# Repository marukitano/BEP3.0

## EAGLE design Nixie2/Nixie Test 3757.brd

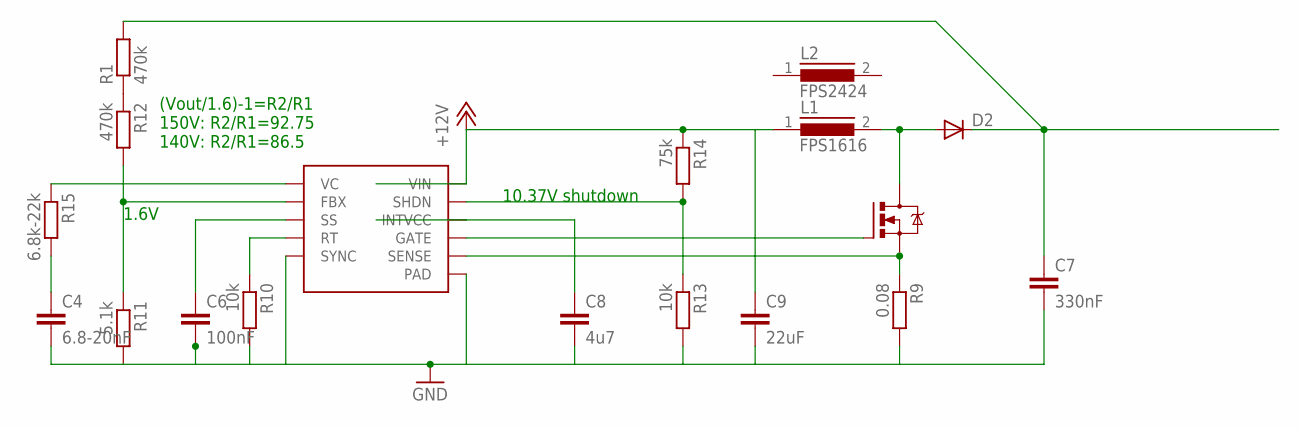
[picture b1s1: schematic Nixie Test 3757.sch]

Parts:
C4: 6.8-20nF; C0805K
C6: 100nF; C0805K
C7: 330nF; C1812
C8: 4u7; C1206K
C9: 22uF; C1210K
D2: DIODE-DO219AB; DO219AB
L1: FPS1616; 1616FPS_22UH
L2: FPS2424; 242408FPS_22UH
Q1: N-MOSFET-TO252-DPAK; TO252
R1, R12: 470k; R0805
R9: 0.08; R0805
R10, R13: 10k; R0805
R11: 5.1k; R0805
R14: 75k; R0805
R15: 6.8k-22k; R0805
U2: LT3757MSOP-10; MSOP-10

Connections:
+12V: C9.1, L1.1, R14.1, U2.10 (VIN)
GND: C4.2, C6.2, C7.2, C8.2, C9.2, R9.2, R10.2, R11.2, R13.2, U2.5 (SYNC), U2.PAD
unnamed: R1.1, R12.1
unnamed: Q1.1 (G), U2.7 (GATE)
unnamed: R11.1, R12.2, U2.2 (FBX)
unnamed: D2.A, L1.2, Q1.3 (D)
unnamed: C7.1, D2.C, R1.2
unnamed: C6.1, U2.3 (SS)
unnamed: R10.1, U2.4 (RT)
unnamed: Q1.2 (S), R9.1, U2.6 (SENSE)
unnamed: R13.1, R14.2, U2.9 (SHDN)
unnamed: C4.1, R15.2
unnamed: R15.1, U2.1 (VC)
unnamed: C8.1, U2.8 (INTVCC)

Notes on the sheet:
10.37V shutdown
1.6V
(Vout/1.6)-1=R2/R1 150V: R2/R1=92.75 140V: R2/R1=86.5

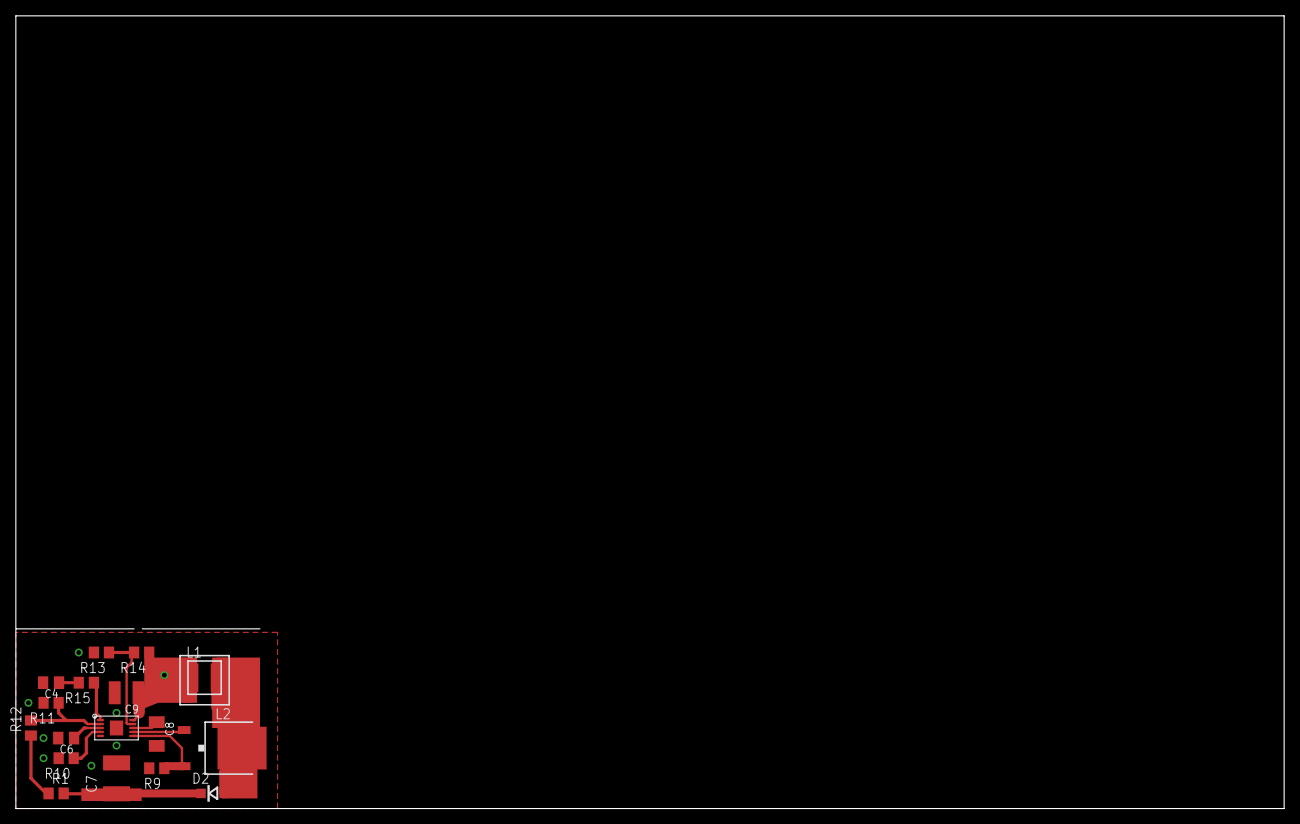
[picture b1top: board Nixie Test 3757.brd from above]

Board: 2 copper layers, 160.0 x 100.0 mm, 18 parts (0 on the bottom side), 14 nets.

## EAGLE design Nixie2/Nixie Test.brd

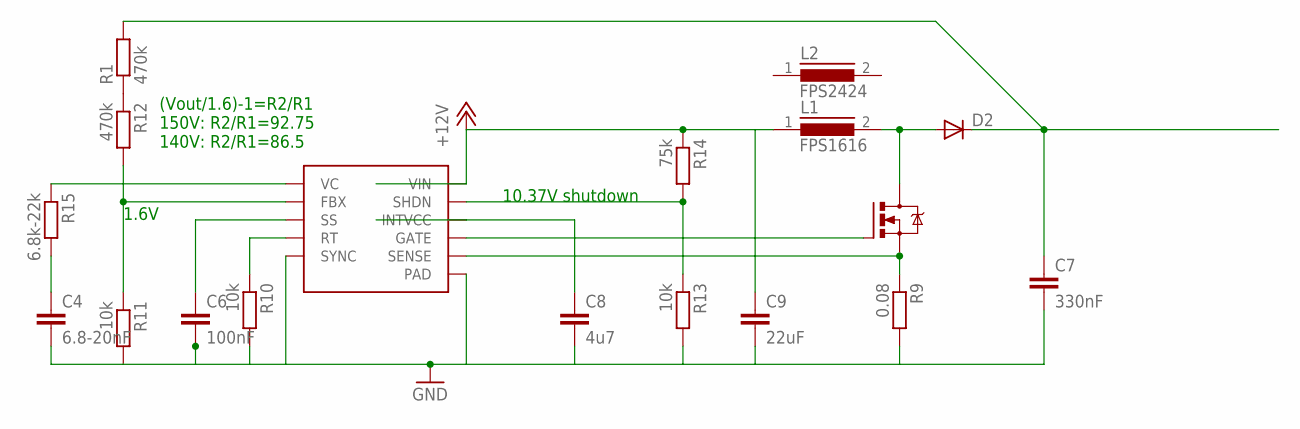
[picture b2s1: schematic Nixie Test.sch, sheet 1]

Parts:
C4: 6.8-20nF; C0805K
C6: 100nF; C0805K
C7: 330nF; C1812
C8: 4u7; C1206K
C9: 22uF; C1210K
D2: DIODE-DO219AB; DO219AB
L1: FPS1616; 1616FPS_22UH
L2: FPS2424; 242408FPS_22UH
Q1: N-MOSFET-TO252-DPAK; TO252
R1, R12: 470k; R0805
R9: 0.08; R0805
R10, R11, R13: 10k; R0805
R14: 75k; R0805
R15: 6.8k-22k; R0805
U2: LT3757MSOP-10; MSOP-10

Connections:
+12V: C9.1, L1.1, R14.1, U2.10 (VIN); also elsewhere on the board
GND: C4.2, C6.2, C7.2, C8.2, C9.2, R9.2, R10.2, R11.2, R13.2, U2.5 (SYNC), U2.PAD; also elsewhere on the board
unnamed: R1.1, R12.1
unnamed: Q1.1 (G), U2.7 (GATE)
unnamed: R11.1, R12.2, U2.2 (FBX)
unnamed: D2.A, L1.2, Q1.3 (D)
unnamed: C7.1, D2.C, R1.2
unnamed: C6.1, U2.3 (SS)
unnamed: R10.1, U2.4 (RT)
unnamed: Q1.2 (S), R9.1, U2.6 (SENSE)
unnamed: R13.1, R14.2, U2.9 (SHDN)
unnamed: C4.1, R15.2
unnamed: R15.1, U2.1 (VC)
unnamed: C8.1, U2.8 (INTVCC)

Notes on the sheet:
10.37V shutdown
1.6V
(Vout/1.6)-1=R2/R1 150V: R2/R1=92.75 140V: R2/R1=86.5

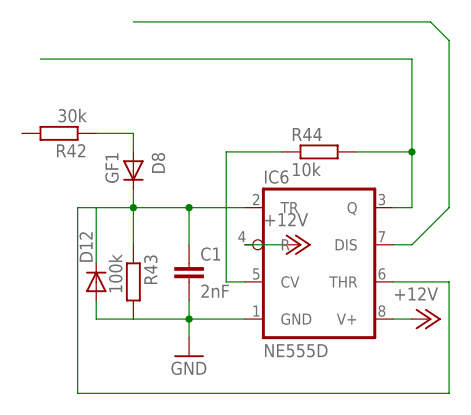
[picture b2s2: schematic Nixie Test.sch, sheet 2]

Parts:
C1: 2nF; C1206K
D8: GF1; SMA-DO214AC
D12: DIODE-DO214AA; DO214AA
IC6: NE555D; SO08
R42: 30k; R0805
R43: 100k; R0805
R44: 10k; R0805

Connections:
+12V: IC6.4 (R), IC6.8 (V+); also elsewhere on the board
GND: C1.2, D12.A, IC6.1 (GND), R43.2; also elsewhere on the board
unnamed: D8.A, R42.1
unnamed: IC6.3 (Q), R44.2
unnamed: IC6.5 (CV), R44.1
unnamed: C1.1, D8.K (C), D12.C, IC6.2 (TR), IC6.6 (THR), R43.1

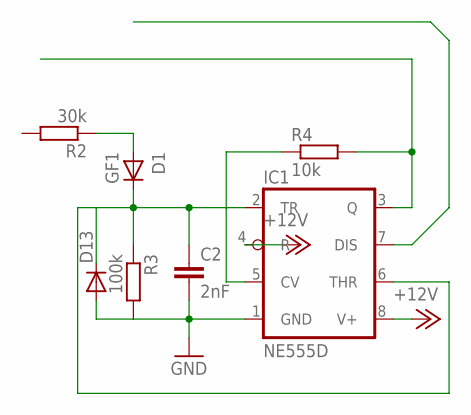
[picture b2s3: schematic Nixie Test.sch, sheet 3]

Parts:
C2: 2nF; C1206K
D1: GF1; SMA-DO214AC
D13: DIODE-DO214AA; DO214AA
IC1: NE555D; SO08
R2: 30k; R0805
R3: 100k; R0805
R4: 10k; R0805

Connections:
+12V: IC1.4 (R), IC1.8 (V+); also elsewhere on the board
GND: C2.2, D13.A, IC1.1 (GND), R3.2; also elsewhere on the board
unnamed: D1.A, R2.1
unnamed: IC1.5 (CV), R4.1
unnamed: C2.1, D1.K (C), D13.C, IC1.2 (TR), IC1.6 (THR), R3.1
unnamed: IC1.3 (Q), R4.2

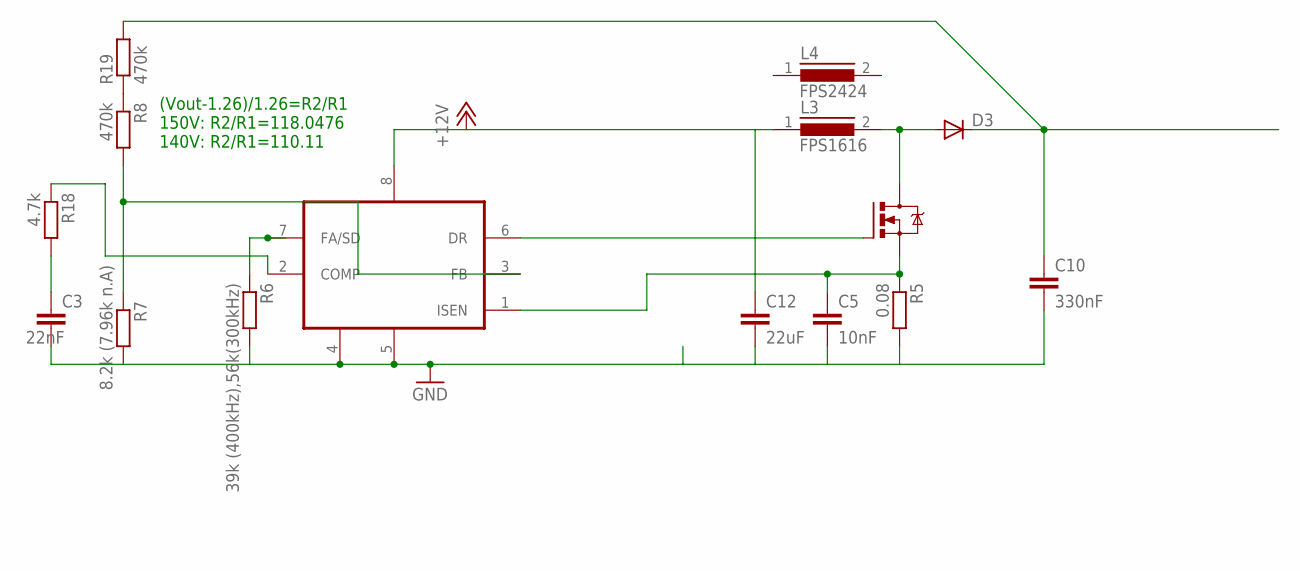
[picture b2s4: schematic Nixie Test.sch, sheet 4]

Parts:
C3: 22nF; C0805K
C5: 10nF; C0805K
C10: 330nF; C1812
C12: 22uF; C1210K
D3: DIODE-DO219AB; DO219AB
L3: FPS1616; 1616FPS_22UH
L4: FPS2424; 242408FPS_22UH
Q2: N-MOSFET-TO252-DPAK; TO252
R5: 0.08; R0805
R6: 39k (400kHz),56k(300kHz); R0805
R7: 8.2k (7.96k n.A); R0805
R8, R19: 470k; R0805
R18: 4.7k; R0805
U3: LM3478; MSOP08

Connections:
+12V: C12.1, L3.1, U3.8 (VIN); also elsewhere on the board
GND: C3.2, C5.2, C10.2, C12.2, R5.2, R6.2, R7.2, U3.4 (AGND), U3.5 (PGND); also elsewhere on the board
unnamed: Q2.1 (G), U3.6 (DR)
unnamed: R7.1, R8.2, U3.3 (FB)
unnamed: D3.A, L3.2, Q2.3 (D)
unnamed: C10.1, D3.C, R19.2
unnamed: R18.1, U3.2 (COMP)
unnamed: R6.1, U3.7 (FA/SD)
unnamed: C5.1, Q2.2 (S), R5.1, U3.1 (ISEN)
unnamed: C3.1, R18.2
unnamed: R8.1, R19.1

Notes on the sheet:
(Vout-1.26)/1.26=R2/R1 150V: R2/R1=118.0476 140V: R2/R1=110.11

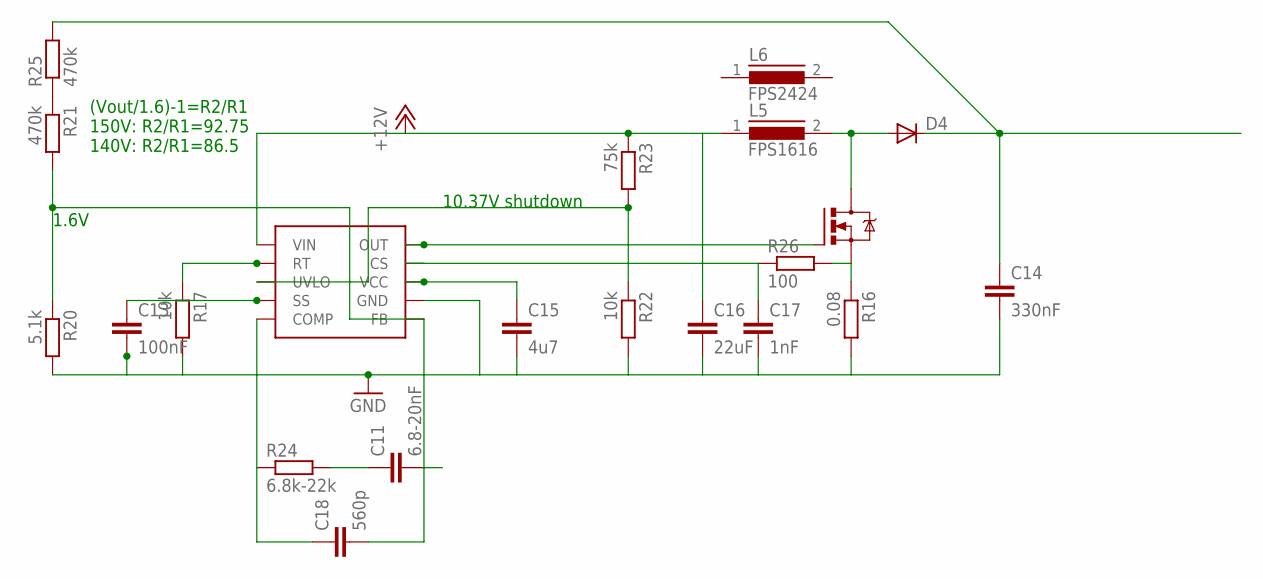
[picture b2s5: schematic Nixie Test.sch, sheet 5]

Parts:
C11: 6.8-20nF; C0805K
C13: 100nF; C0805K
C14: 330nF; C1812
C15: 4u7; C1206K
C16: 22uF; C1210K
C17: 1nF; C0805K
C18: 560p; C0805K
D4: DIODE-DO219AB; DO219AB
L5: FPS1616; 1616FPS_22UH
L6: FPS2424; 242408FPS_22UH
Q3: N-MOSFET-TO252-DPAK; TO252
R16: 0.08; R0805
R17, R22: 10k; R0805
R20: 5.1k; R0805
R21, R25: 470k; R0805
R23: 75k; R0805
R24: 6.8k-22k; R0805
R26: 100; R0805
U4: LM5022MSOP-10; MSOP-10-NOPAD

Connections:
+12V: C16.1, L5.1, R23.1, U4.1 (VIN); also elsewhere on the board
GND: C13.2, C14.2, C15.2, C16.2, C17.2, R16.2, R17.2, R20.2, R22.2, U4.6 (GND); also elsewhere on the board
unnamed: Q3.1 (G), U4.5 (OUT)
unnamed: C11.2, C18.2, R20.1, R21.2, U4.2 (FB)
unnamed: D4.A, L5.2, Q3.3 (D)
unnamed: C14.1, D4.C, R25.2
unnamed: C13.1, U4.10 (SS)
unnamed: R17.1, U4.9 (RT)
unnamed: Q3.2 (S), R16.1, R26.2
unnamed: R22.1, R23.2, U4.7 (UVLO)
unnamed: C11.1, R24.2
unnamed: C18.1, R24.1, U4.3 (COMP)
unnamed: C15.1, U4.4 (VCC)
unnamed: R21.1, R25.1
unnamed: C17.1, R26.1, U4.8 (CS)

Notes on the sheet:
10.37V shutdown
1.6V
(Vout/1.6)-1=R2/R1 150V: R2/R1=92.75 140V: R2/R1=86.5

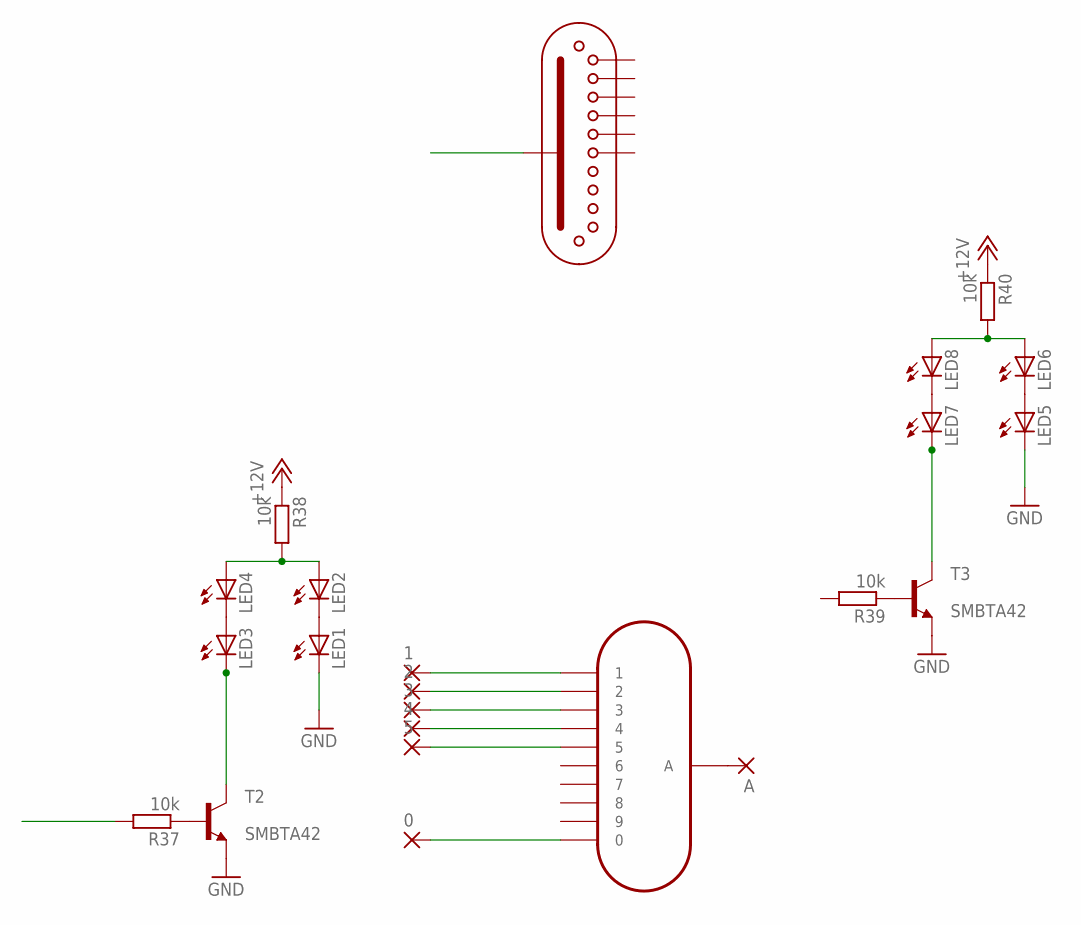
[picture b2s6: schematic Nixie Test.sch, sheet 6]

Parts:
0, 1, 2, 3, 4, 5: SMD2; SMD1,27-2,54
A: SMD2; SMD1,27-2,54
LED1, LED2, LED3, LED4, LED5, LED6, LED7, LED8: LED3MM
N1: IN-12A-IN-12; IN-12
R37, R38, R39, R40: 10k; R0805
T2, T3: MMBTA42LT1-NPN-SOT23-BEC; SOT23-BEC
U$3: ZM1020

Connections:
+12V: R38.1, R40.1; also elsewhere on the board
GND: LED1.K (C), LED5.K (C), T2.E, T3.E; also elsewhere on the board
unnamed: LED1.A, LED2.K (C)
unnamed: LED3.A, LED4.K (C)
unnamed: R37.1, T2.B
unnamed: LED3.K (C), T2.C
unnamed: LED2.A, LED4.A, R38.2
unnamed: 0.1, N1.0
unnamed: 1.1, N1.1
unnamed: 2.1, N1.2
unnamed: 3.1, N1.3
unnamed: 4.1, N1.4
unnamed: 5.1, N1.5
unnamed: A.1, N1.A
unnamed: LED5.A, LED6.K (C)
unnamed: LED7.A, LED8.K (C)
unnamed: R39.1, T3.B
unnamed: LED7.K (C), T3.C
unnamed: LED6.A, LED8.A, R40.2

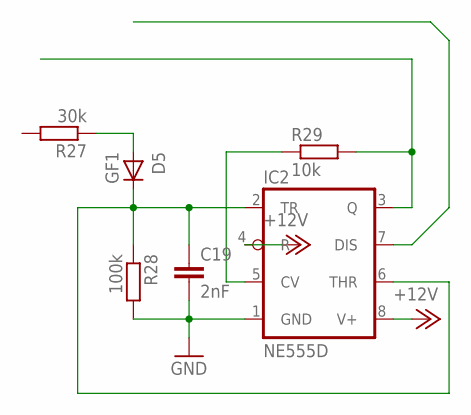
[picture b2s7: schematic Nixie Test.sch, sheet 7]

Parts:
C19: 2nF; C1206K
D5: GF1; SMA-DO214AC
IC2: NE555D; SO08
R27: 30k; R0805
R28: 100k; R0805
R29: 10k; R0805

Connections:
+12V: IC2.4 (R), IC2.8 (V+); also elsewhere on the board
GND: C19.2, IC2.1 (GND), R28.2; also elsewhere on the board
unnamed: D5.A, R27.1
unnamed: IC2.5 (CV), R29.1
unnamed: C19.1, D5.K (C), IC2.2 (TR), IC2.6 (THR), R28.1
unnamed: IC2.3 (Q), R29.2

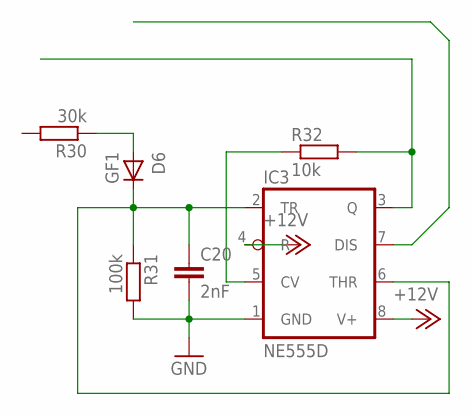
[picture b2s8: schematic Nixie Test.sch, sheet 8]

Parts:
C20: 2nF; C1206K
D6: GF1; SMA-DO214AC
IC3: NE555D; SO08
R30: 30k; R0805
R31: 100k; R0805
R32: 10k; R0805

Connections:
+12V: IC3.4 (R), IC3.8 (V+); also elsewhere on the board
GND: C20.2, IC3.1 (GND), R31.2; also elsewhere on the board
unnamed: D6.A, R30.1
unnamed: IC3.5 (CV), R32.1
unnamed: C20.1, D6.K (C), IC3.2 (TR), IC3.6 (THR), R31.1
unnamed: IC3.3 (Q), R32.2

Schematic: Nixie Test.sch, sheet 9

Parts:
C21: 2nF; C1206K
D7: GF1; SMA-DO214AC
IC4: NE555D; SO08
R33: 30k; R0805
R34: 100k; R0805
R35: 10k; R0805

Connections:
+12V: IC4.4 (R), IC4.8 (V+); also elsewhere on the board
GND: C21.2, IC4.1 (GND), R34.2; also elsewhere on the board
unnamed: D7.A, R33.1
unnamed: IC4.5 (CV), R35.1
unnamed: C21.1, D7.K (C), IC4.2 (TR), IC4.6 (THR), R34.1
unnamed: IC4.3 (Q), R35.2

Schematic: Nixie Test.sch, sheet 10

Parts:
C22: 2nF; C1206K
D9: GF1; SMA-DO214AC
IC5: NE555D; SO08
R36: 30k; R0805
R41: 100k; R0805
R45: 10k; R0805

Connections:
+12V: IC5.4 (R), IC5.8 (V+); also elsewhere on the board
GND: C22.2, IC5.1 (GND), R41.2; also elsewhere on the board
unnamed: D9.A, R36.1
unnamed: IC5.5 (CV), R45.1
unnamed: C22.1, D9.K (C), IC5.2 (TR), IC5.6 (THR), R41.1
unnamed: IC5.3 (Q), R45.2

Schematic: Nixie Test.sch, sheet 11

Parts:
C23: 6.8-20nF; C0805K
C24: 100nF; C0805K
C25: 330nF; C1812
C26: 4u7; C1206K
C27: 22uF; C1210K
D10: DIODE-DO219AB; DO219AB
L7: FPS1616; 1616FPS_22UH
L8: FPS2424; 242408FPS_22UH
Q4: N-MOSFET-TO252-DPAK; TO252
R46: 0.08; R0805
R47, R50: 10k; R0805
R48: 5.1k; R0805
R49, R53: 470k; R0805
R51: 75k; R0805
R52: 6.8k-22k; R0805
U1: LT3757MSOP-10; MSOP-10

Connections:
+12V: C27.1, L7.1, R51.1, U1.10 (VIN); also elsewhere on the board
GND: C23.2, C24.2, C25.2, C26.2, C27.2, R46.2, R47.2, R48.2, R50.2, U1.5 (SYNC), U1.PAD; also elsewhere on the board
unnamed: Q4.1 (G), U1.7 (GATE)
unnamed: R48.1, R49.2, U1.2 (FBX)
unnamed: D10.A, L7.2, Q4.3 (D)
unnamed: C25.1, D10.C, R53.2
unnamed: C24.1, U1.3 (SS)
unnamed: R47.1, U1.4 (RT)
unnamed: Q4.2 (S), R46.1, U1.6 (SENSE)
unnamed: R50.1, R51.2, U1.9 (SHDN)
unnamed: C23.1, R52.2
unnamed: R52.1, U1.1 (VC)
unnamed: C26.1, U1.8 (INTVCC)
unnamed: R49.1, R53.1

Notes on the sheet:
10.37V shutdown
1.6V
(Vout/1.6)-1=R2/R1 150V: R2/R1=92.75 140V: R2/R1=86.5

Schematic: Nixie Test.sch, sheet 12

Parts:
C28: 2nF; C1206K
D11: GF1; SMA-DO214AC
IC7: NE555D; SO08
R54: 30k; R0805
R55: 100k; R0805
R56: 10k; R0805

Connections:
+12V: IC7.4 (R), IC7.8 (V+); also elsewhere on the board
GND: C28.2, IC7.1 (GND), R55.2; also elsewhere on the board
unnamed: D11.A, R54.1
unnamed: IC7.5 (CV), R56.1
unnamed: C28.1, D11.K (C), IC7.2 (TR), IC7.6 (THR), R55.1
unnamed: IC7.3 (Q), R56.2

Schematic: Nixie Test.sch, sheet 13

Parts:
12, 13, 14, 15, 16, 17, 18, 19, 20, 21: SMD2; SMD1,27-2,54
A2: SMD2; SMD1,27-2,54
LED17, LED18, LED19, LED20: LED_PLCC6; PLCC6
LED21, LED22: LED_LRTB_G6TG; PLCC6
N3: IN-12A-IN-12; IN-12
R71, R72, R73, R74, R75, R76, R77, R78: 10k; R0805
U$5, U$6, U$8, U$9, U$12, U$13: PLCC2
U$7, U$10, U$11: ZM1020

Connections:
GND: LED18.C3 (C), LED20.C3 (C), LED22.C2 (C), LED22.C3 (C), U$8.C, U$9.C, U$12.C, U$13.C; also elsewhere on the board
unnamed: U$5.C, U$8.A
unnamed: U$6.C, U$9.A
unnamed: R72.2, U$6.A
unnamed: R71.2, U$5.A
unnamed: 12.1, R71.1, R72.1
unnamed: LED17.C3 (C), LED18.A3 (A)
unnamed: LED19.C3 (C), LED20.A3 (A)
unnamed: LED19.A3 (A), R74.2
unnamed: LED17.A3 (A), R73.2
unnamed: 13.1, R73.1, R74.1
unnamed: LED21.C2 (C), LED22.A2 (A)
unnamed: LED21.C3 (C), LED22.A3 (A)
unnamed: LED21.A3 (A), R76.2
unnamed: LED21.A2 (A), R75.2
unnamed: 14.1, R75.1, R76.1
unnamed: 15.1, N3.0
unnamed: 16.1, N3.1
unnamed: 17.1, N3.2
unnamed: 18.1, N3.3
unnamed: 19.1, N3.4
unnamed: 20.1, N3.5
unnamed: A2.1, N3.A
unnamed: R78.2, U$13.A
unnamed: R77.2, U$12.A
unnamed: 21.1, R77.1, R78.1

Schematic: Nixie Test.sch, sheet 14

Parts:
D14, D15, D16: 1N4148; SOD323-W
PAD1, PAD2, PAD3, PAD4: WIREPAD1,6/0,8; 1,6/0,8
R57, R58, R59: R-EU_R0805; R0805
T1, T4, T5: BSP78; SOT223
X3: F09D

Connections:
CTS: R57.1, X3.8; also elsewhere on the board
DCD: R59.1, X3.1; also elsewhere on the board
DSR: R58.1, X3.6; also elsewhere on the board
DTR: D16.A, X3.4; also elsewhere on the board
GND: PAD4.1, T1.3 (S), T4.3 (S), T5.3 (S), X3.5; also elsewhere on the board
unnamed: D16.C, T5.1 (G)
unnamed: D15.C, T4.1 (G)
unnamed: D14.C, T1.1 (G)
unnamed: PAD1.1, R57.2, T1.2 (D)
unnamed: PAD2.1, R58.2, T4.2 (D)
unnamed: PAD3.1, R59.2, T5.2 (D)
unnamed: D14.A, X3.7
RTS: D15.A, X3.3; also elsewhere on the board

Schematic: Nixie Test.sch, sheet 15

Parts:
D17, D18, D19: 1N4148; SOD323-W
PAD5, PAD6, PAD7, PAD8: WIREPAD1,6/0,8; 1,6/0,8
R60, R61, R62: R-EU_R0805; R0805
T6, T7, T8: BSP78; SOT223
X1: F09D

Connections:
CTS: R60.1, X1.8; also elsewhere on the board
DCD: R62.1, X1.1; also elsewhere on the board
DSR: R61.1, X1.6; also elsewhere on the board
DTR: D19.A, X1.4; also elsewhere on the board
GND: PAD8.1, T6.3 (S), T7.3 (S), T8.3 (S), X1.5; also elsewhere on the board
unnamed: D19.C, T8.1 (G)
unnamed: D18.C, T7.1 (G)
unnamed: D17.C, T6.1 (G)
unnamed: PAD5.1, R60.2, T6.2 (D)
unnamed: PAD6.1, R61.2, T7.2 (D)
unnamed: PAD7.1, R62.2, T8.2 (D)
unnamed: D17.A, X1.7
RTS: D18.A, X1.3; also elsewhere on the board

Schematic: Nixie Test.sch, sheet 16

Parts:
D20, D21, D22: 1N4148; SOD323-W
PAD9, PAD10, PAD11, PAD12: WIREPAD1,6/0,8; 1,6/0,8
R63, R64, R65: R-EU_R0805; R0805
T9, T10, T11: BSP78; SOT223
X2: F09D

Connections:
CTS: R63.1, X2.8; also elsewhere on the board
DCD: R65.1, X2.1; also elsewhere on the board
DSR: R64.1, X2.6; also elsewhere on the board
DTR: D22.A, X2.4; also elsewhere on the board
GND: PAD12.1, T9.3 (S), T10.3 (S), T11.3 (S), X2.5; also elsewhere on the board
unnamed: D22.C, T11.1 (G)
unnamed: D21.C, T10.1 (G)
unnamed: D20.C, T9.1 (G)
unnamed: PAD9.1, R63.2, T9.2 (D)
unnamed: PAD10.1, R64.2, T10.2 (D)
unnamed: PAD11.1, R65.2, T11.2 (D)
unnamed: D20.A, X2.7
RTS: D21.A, X2.3; also elsewhere on the board

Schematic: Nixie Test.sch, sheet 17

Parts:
D24, D25, D26: 1N4148; SOD323-W
PAD13, PAD14, PAD15, PAD16: WIREPAD1,6/0,8; 1,6/0,8
R66, R67, R68: R-EU_R0805; R0805
T12, T13, T14: BSP78; SOT223
X4: F09D

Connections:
CTS: R66.1, X4.8; also elsewhere on the board
DCD: R68.1, X4.1; also elsewhere on the board
DSR: R67.1, X4.6; also elsewhere on the board
DTR: D26.A, X4.4; also elsewhere on the board
GND: PAD16.1, T12.3 (S), T13.3 (S), T14.3 (S), X4.5; also elsewhere on the board
unnamed: D26.C, T14.1 (G)
unnamed: D25.C, T13.1 (G)
unnamed: D24.C, T12.1 (G)
unnamed: PAD13.1, R66.2, T12.2 (D)
unnamed: PAD14.1, R67.2, T13.2 (D)
unnamed: PAD15.1, R68.2, T14.2 (D)
unnamed: D24.A, X4.7
RTS: D25.A, X4.3; also elsewhere on the board

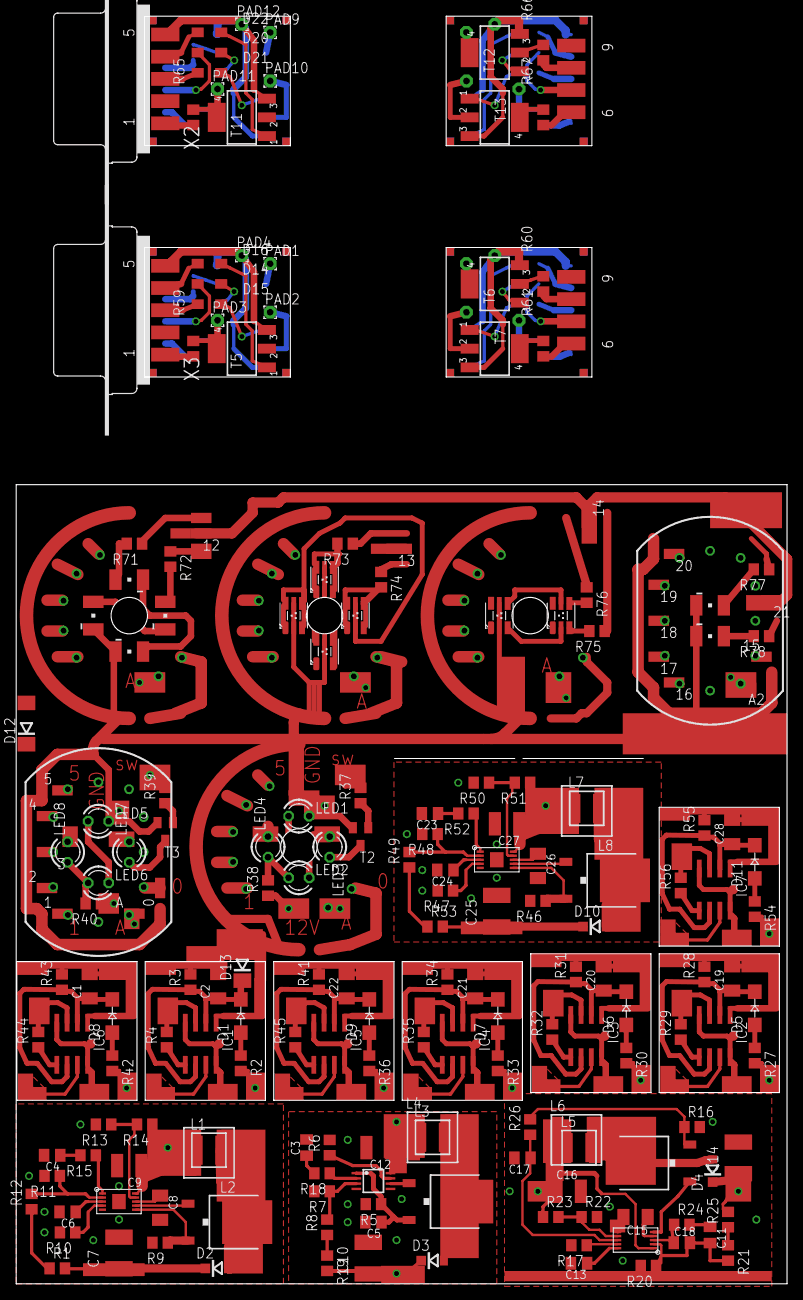
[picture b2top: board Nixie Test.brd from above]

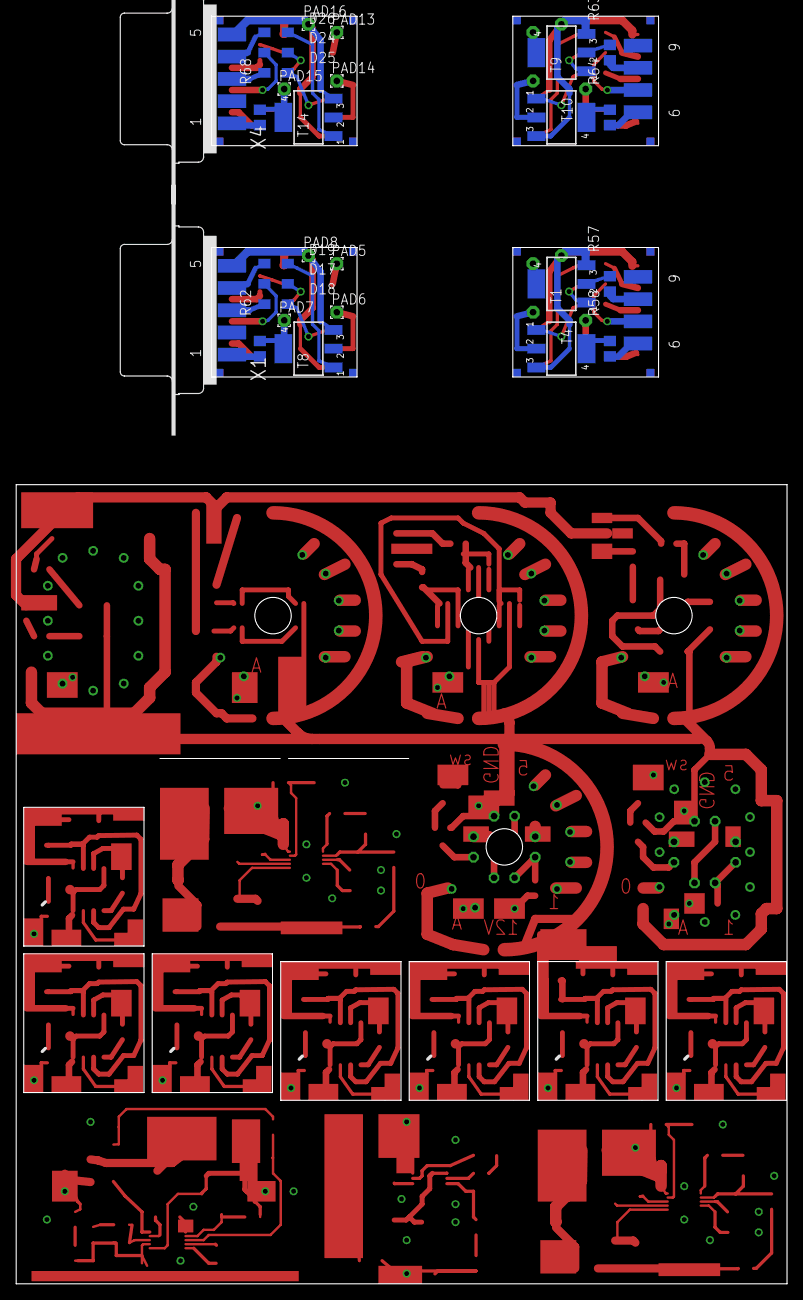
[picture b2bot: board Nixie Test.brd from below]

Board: 2 copper layers, 95.2 x 156.6 mm, 230 parts (28 on the bottom side), 151 nets.

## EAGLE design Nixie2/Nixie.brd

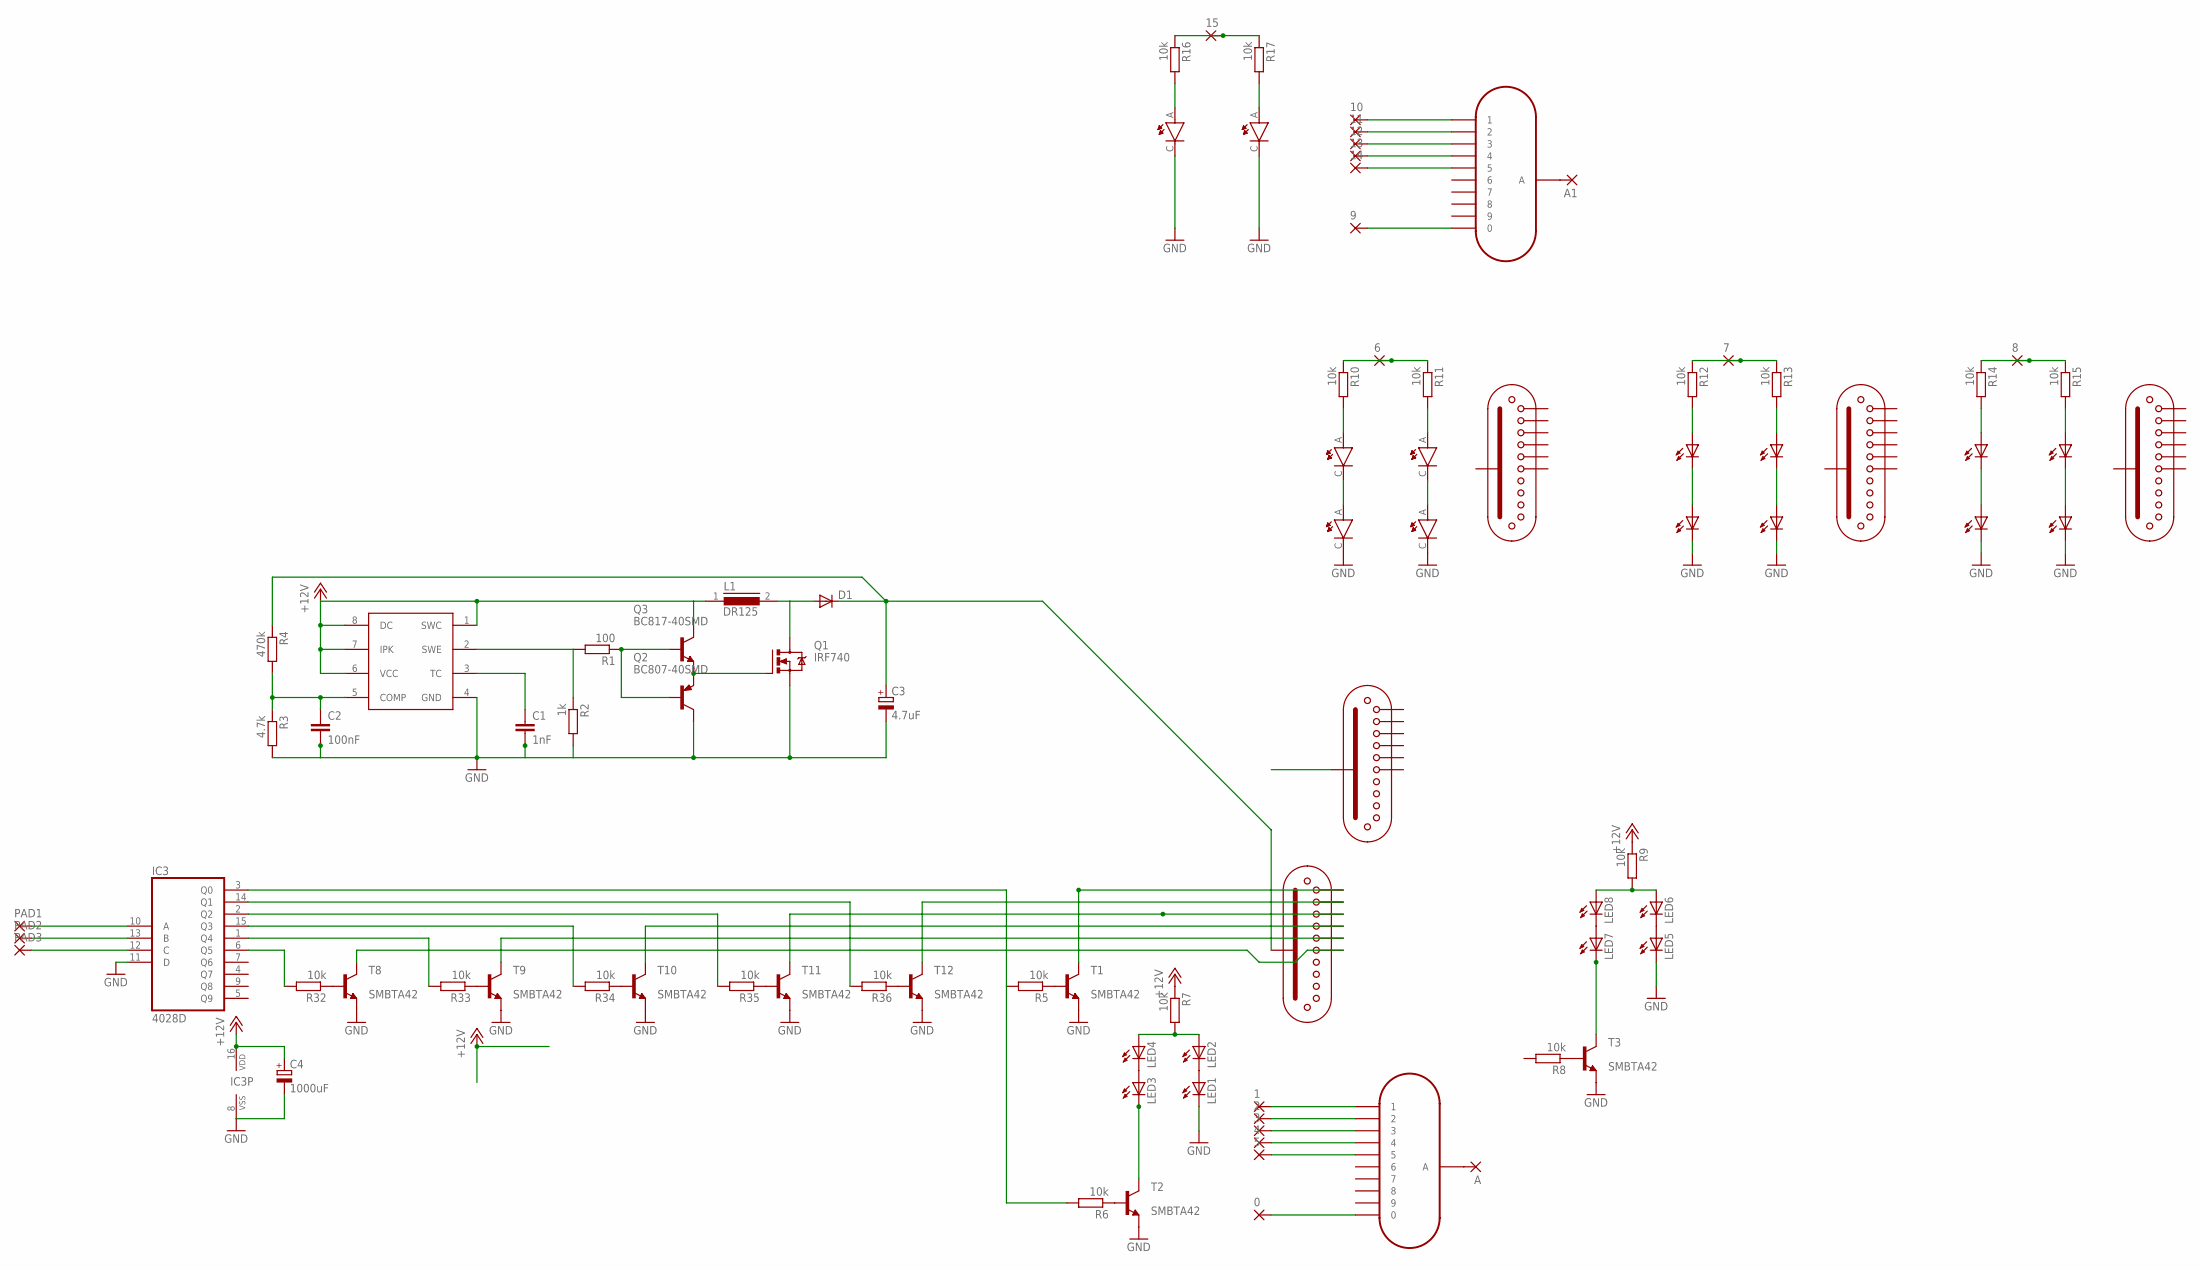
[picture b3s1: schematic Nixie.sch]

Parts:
0, 1, 2, 3, 4, 5, 6, 7, 8, 9, 10, 11, 12, 13, 14, 15: SMD2; SMD1,27-2,54
A, A1: SMD2; SMD1,27-2,54
C1: 1nF; C0805K
C2: 100nF; C0805K
C3: 4.7uF; E5-10,5
C4: 1000uF; E5-10,5
D1: DIODE-DO214AC; DO214AC
IC3: 4028D; SO16
L1: DR125
LED1, LED2, LED3, LED4, LED5, LED6, LED7, LED8: LED3MM
LED9, LED10, LED11, LED12: LED_PLCC6; PLCC6
LED13, LED14: LED_LRTB_G6TG; PLCC6
N1, N2: IN-12A-IN-12; IN-12
PAD1, PAD2, PAD3: 1,6/0,8
Q1: IRF740; TO220BV
Q2: BC807-40SMD; SOT23-BEC
Q3: BC817-40SMD; SOT23-BEC
R1: 100; R0805
R2: 1k; R0805
R3: 4.7k; R0805
R4: 470k; R0805
R5, R6, R7, R8, R9, R10, R11, R12, R13, R14, R15, R16, R17, R32, R33, R34, R35, R36: 10k; R0805
T1, T2, T3, T8, T9, T10, T11, T12: MMBTA42LT1-NPN-SOT23-BEC; SOT23-BEC
U$1, U$3, U$6, U$9, U$11: ZM1020
U$2: MC33063/MC34063D; SO08
U$4, U$5, U$7, U$8, U$10, U$12: PLCC2

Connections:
+12V: C4.+, IC3.16 (VDD), L1.1, Q3.C, R7.1, R9.1, U$2.1 (SWC), U$2.6 (VCC), U$2.7 (IPK), U$2.8 (DC)
GND: C1.2, C2.2, C3.-, C4.-, IC3.8 (VSS), IC3.11 (D), LED1.K (C), LED5.K (C), LED10.C3 (C), LED12.C3 (C), LED14.C2 (C), LED14.C3 (C), Q1.S, Q2.C, R2.2, R3.2, T1.E, T2.E, T3.E, T8.E, T9.E, T10.E, T11.E, T12.E, U$2.4 (GND), U$7.C, U$8.C, U$10.C, U$12.C
unnamed: C1.1, U$2.3 (TC)
unnamed: IC3.10 (A), PAD1.1
unnamed: IC3.13 (B), PAD2.1
unnamed: D1.A, L1.2, Q1.D
unnamed: C2.1, R3.1, R4.2, U$2.5 (COMP)
unnamed: IC3.3 (Q0), R5.2, R6.2
unnamed: R1.2, R2.1, U$2.2 (SWE)
unnamed: C3.+, D1.C, R4.1, U$1.12 (A)
unnamed: Q1.G, Q2.E, Q3.E
unnamed: Q2.B, Q3.B, R1.1
unnamed: IC3.12 (C), PAD3.1
unnamed: R5.1, T1.B
unnamed: T1.C, U$1.11 (0)
unnamed: LED1.A, LED2.K (C)
unnamed: LED3.A, LED4.K (C)
unnamed: R6.1, T2.B
unnamed: R32.1, T8.B
unnamed: LED3.K (C), T2.C
unnamed: LED2.A, LED4.A, R7.2
unnamed: 0.1, N1.0
unnamed: 1.1, N1.1
unnamed: 2.1, N1.2
unnamed: 3.1, N1.3
unnamed: 4.1, N1.4
unnamed: 5.1, N1.5
unnamed: IC3.14 (Q1), R36.2
unnamed: IC3.2 (Q2), R35.2
unnamed: T10.C, U$1.3
unnamed: A.1, N1.A
unnamed: LED5.A, LED6.K (C)
unnamed: LED7.A, LED8.K (C)
unnamed: R8.1, T3.B
unnamed: LED7.K (C), T3.C
unnamed: LED6.A, LED8.A, R9.2
unnamed: T9.C, U$1.4
unnamed: R34.1, T10.B
unnamed: U$4.C, U$7.A
unnamed: U$5.C, U$8.A
unnamed: R11.2, U$5.A
unnamed: R10.2, U$4.A
unnamed: R33.1, T9.B
unnamed: R35.1, T11.B
unnamed: 6.1, R10.1, R11.1
unnamed: LED11.C3 (C), LED12.A3 (A)
unnamed: IC3.6 (Q5), R32.2
unnamed: R36.1, T12.B
unnamed: T8.C, U$1.5
unnamed: IC3.1 (Q4), R33.2
unnamed: IC3.15 (Q3), R34.2
unnamed: T11.C, U$1.2
unnamed: T12.C, U$1.1
unnamed: LED11.A3 (A), R13.2
unnamed: LED9.A3 (A), R12.2
unnamed: 7.1, R12.1, R13.1
unnamed: LED9.C3 (C), LED10.A3 (A)
unnamed: LED13.C2 (C), LED14.A2 (A)
unnamed: LED13.C3 (C), LED14.A3 (A)
unnamed: LED13.A3 (A), R15.2
unnamed: LED13.A2 (A), R14.2
unnamed: 8.1, R14.1, R15.1
unnamed: 9.1, N2.0
unnamed: 10.1, N2.1
unnamed: 11.1, N2.2
unnamed: 12.1, N2.3
unnamed: 13.1, N2.4
unnamed: 14.1, N2.5
unnamed: A1.1, N2.A
unnamed: R17.2, U$12.A
unnamed: R16.2, U$10.A
unnamed: 15.1, R16.1, R17.1

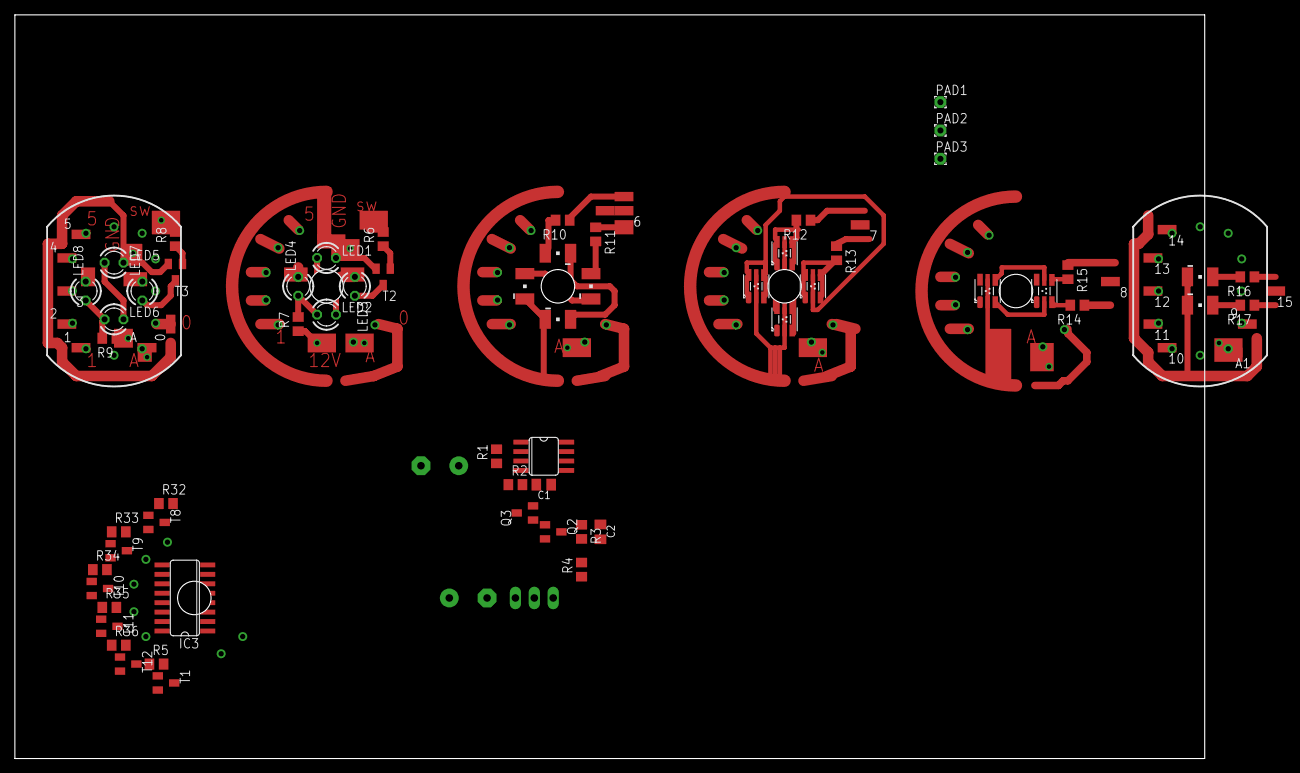
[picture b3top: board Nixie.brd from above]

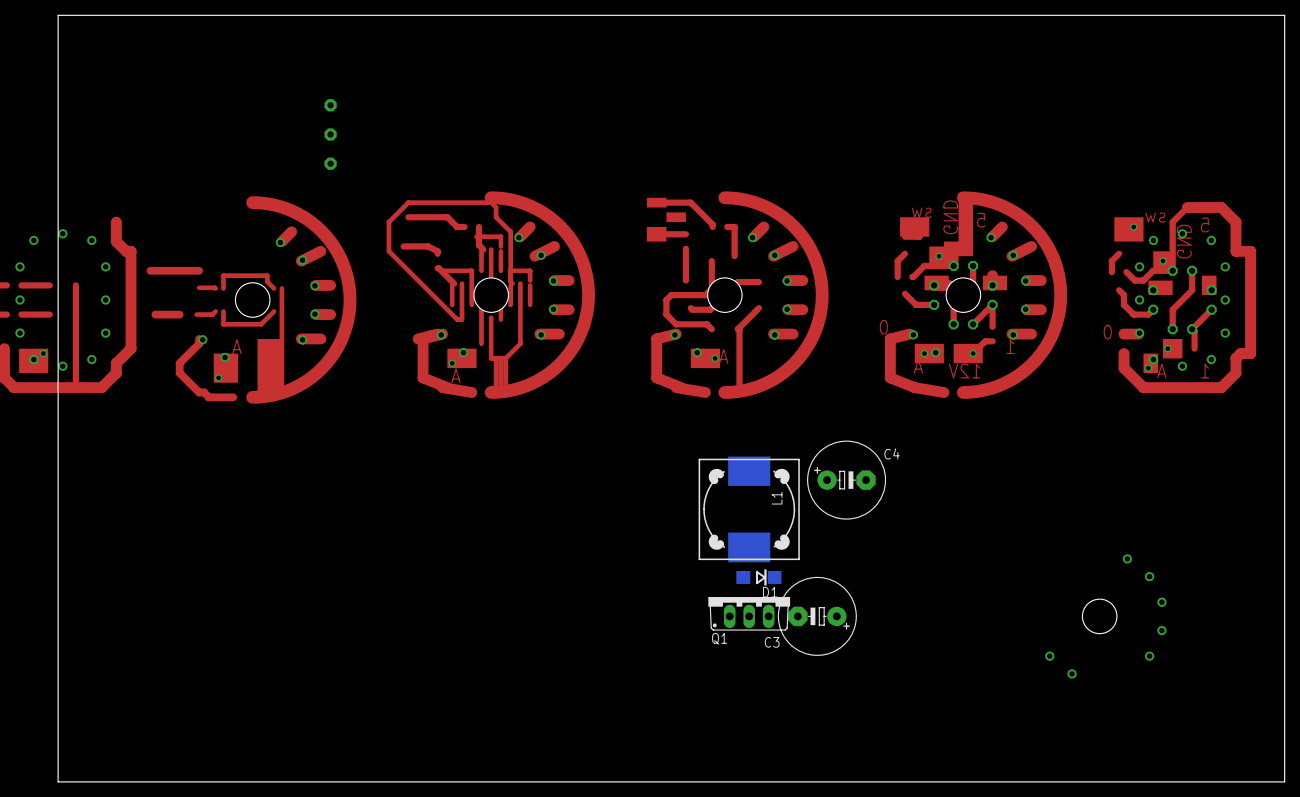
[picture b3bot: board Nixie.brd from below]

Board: 2 copper layers, 160.0 x 100.0 mm, 89 parts (5 on the bottom side), 72 nets.

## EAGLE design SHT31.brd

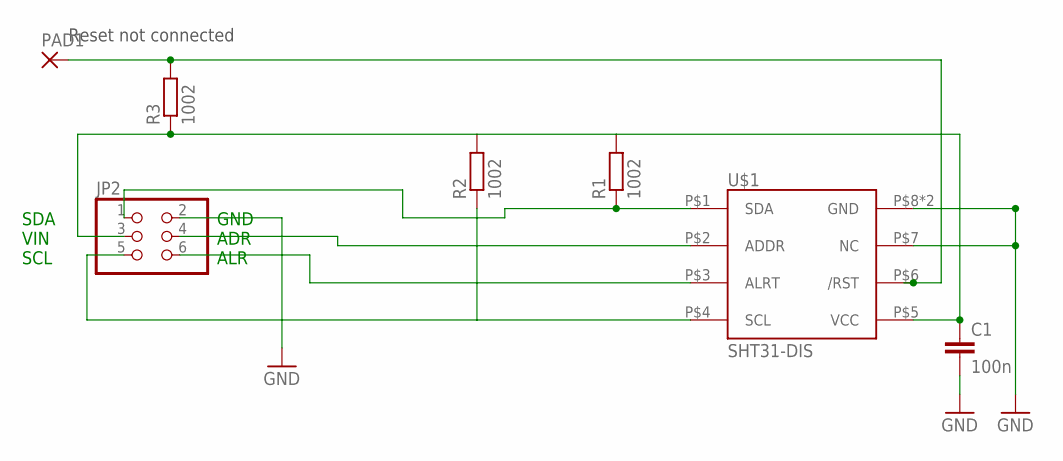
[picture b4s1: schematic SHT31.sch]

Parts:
C1: 100n; C0805K
JP2: PINHD-2X3; 2X03
PAD1: 1,6/0,8
R1, R2, R3: 1002; R0805
U$1: SHT31-DIS; SHT3X

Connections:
GND: C1.2, JP2.2, U$1.P$7 (NC), U$1.P$8 (GND), U$1.PAD (GND)
unnamed: JP2.5, R2.1, U$1.P$4 (SCL)
unnamed: JP2.1, R1.1, U$1.P$1 (SDA)
unnamed: JP2.4, U$1.P$2 (ADDR)
unnamed: JP2.6, U$1.P$3 (ALRT)
unnamed: PAD1.1, R3.2, U$1.P$6 (/RST)
unnamed: C1.1, JP2.3, R1.2, R2.2, R3.1, U$1.P$5 (VCC)

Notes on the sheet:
SDA VIN SCL
GND ADR ALR
Reset not connected

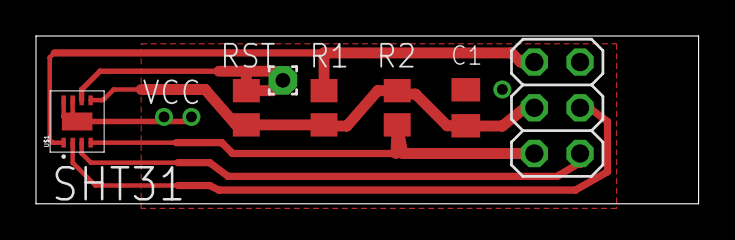
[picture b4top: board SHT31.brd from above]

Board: 2 copper layers, 36.8 x 9.3 mm, 7 parts (0 on the bottom side), 7 nets.
